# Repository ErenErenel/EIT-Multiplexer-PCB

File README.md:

# EIT Multiplexer PCB

EE499 Capstone Project — Low-power analog multiplexer board for Electrical Impedance Tomography (EIT).

## Overview

This board drives a 16-channel analog multiplexer (ADG1606) controlled by an RP2040 microcontroller. It is designed for EIT data acquisition, where the multiplexer selects electrode channels to inject current and measure voltage.

**Key ICs:**
- Raspberry Pi RP2040 — microcontroller
- ADG1606 — 16:1 analog multiplexer
- AP2112K — 5V to 3.3V LDO regulator
- LM27761 — negative voltage converter (for symmetric supply)

## Repository Structure

```
Hardware/         — KiCad project files (.kicad_pro, .kicad_sch, .kicad_pcb)
                    Custom footprint and symbol libraries bundled for portability
Production/
  Gerbers/        — Gerber files + drill files ready for PCB fabrication
  BOM/            — Bill of Materials (CSV and XLSX)
Docs/             — Schematic PDF, assembly drawing, component datasheets
```

## Opening the Design

1. Open **KiCad** (v7 or later)
2. Open `Hardware/EIT_Multiplexer.kicad_pro`
3. All custom libraries load automatically via relative paths — no manual configuration needed

## Fabrication

Gerber files are in `Production/Gerbers/`. The board is 2-layer FR4. Upload the contents of that folder (or `EIT_Multiplexer-job.gbrjob`) to your preferred PCB fab (JLCPCB, PCBWay, OSH Park, etc.).

## License

Hardware design files licensed under [CERN Open Hardware Licence v2 – Strongly Reciprocal (CERN-OHL-S)](LICENSE).

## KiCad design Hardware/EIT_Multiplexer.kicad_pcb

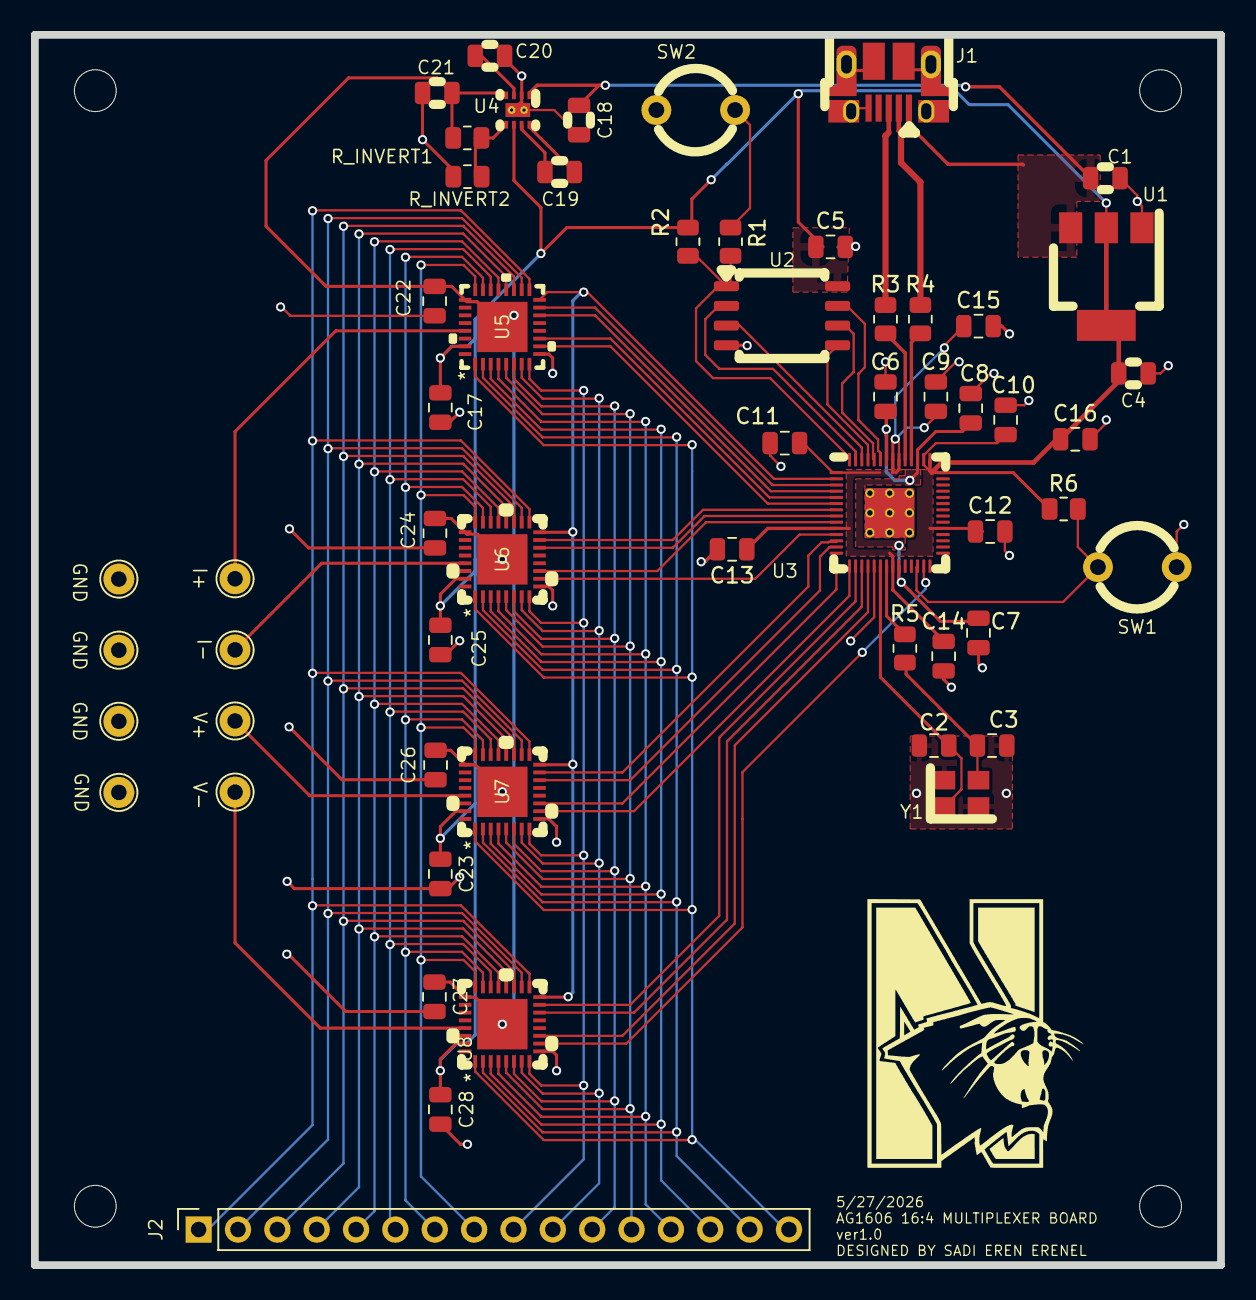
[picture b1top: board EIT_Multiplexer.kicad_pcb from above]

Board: 2 copper layers, 76.5 x 79.4 mm, 61 parts (0 on the bottom side), 61 nets.

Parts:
C1, C4: 10u; C_0805_2012Metric
C2, C3: 15p; C_0805_2012Metric
C5, C6, C7, C9, C11, C12, C13, C14, C15, C16, C17, C22, C23, C24, C25, C26, C27, C28: 100n; C_0805_2012Metric
C8, C10, C19: 1u; C_0805_2012Metric
C18, C20: 4.7u; C_0805_2012Metric
C21: 2.2u; C_0805_2012Metric
GND: Conn_01x01_Pin; TestPoint_THTPad_D2.0mm_Drill1.0mm
GND#2, GND#3, GND#4: Conn_01x01_Pin; TestPoint_THTPad_D2.0mm_Drill1.0mm
H1, H2, H3, H4: MountingHole; MountingHole_2.7mm_M2.5
I+: Conn_01x01_Pin; TestPoint_THTPad_D2.0mm_Drill1.0mm
I-: Conn_01x01_Pin; TestPoint_THTPad_D2.0mm_Drill1.0mm
J1: USB_B_Micro; USB_Micro-B_Amphenol_10103594-0001LF_Horizontal_modified
J2: Conn_01x16_Pin; PinSocket_1x16_P2.54mm_Vertical
R1, R5: 1k; R_0805_2012Metric
R2, R6: 10k; R_0805_2012Metric
R3, R4: 27; R_0805_2012Metric
R_INVERT1, R_INVERT2: R; R_0805_2012Metric
SW1, SW2: SW_Push; pushbutton (1)
U1: NCP1117-3.3_SOT223; SOT-223-3_TabPin2
U2: W25Q128JVS; SOIC-8_5.3x5.3mm_P1.27mm
U3: RP2040; RP2040-QFN-56
U4: LM27761DSGR; DSG0008A
U5, U6, U7, U8: ADG1606BCPZ-REEL7; CP_32_2_ADI
V+: Conn_01x01_Pin; TestPoint_THTPad_D2.0mm_Drill1.0mm
V-: Conn_01x01_Pin; TestPoint_THTPad_D2.0mm_Drill1.0mm
Y1: ABM8-272-T3; Crystal_SMD_3225-4Pin_3.2x2.5mm

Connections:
+1V1: C6.1, C7.1, C8.1, U3.23 (DVDD), U3.45 (VREG_VOUT), U3.50 (DVDD)
+3V3: C4.1, C5.1, C9.1, C10.1, C11.1, C12.1, C13.1, C14.1, C15.1, C16.1, C17.1, C23.1, C25.1, C28.1, R2.1, R6.1, U1.2 (VO), U2.8 (VCC), U3.1 (IOVDD), U3.10 (IOVDD), U3.22 (IOVDD), U3.33 (IOVDD), U3.42 (IOVDD), U3.43 (ADC_AVDD), U3.44 (VREG_IN), U3.48 (USB_VDD), U3.49 (IOVDD), U4.6 (EN), U5.31 (VDD), U6.31 (VDD), U7.31 (VDD), U8.31 (VDD)
-3V3: C21.1, C22.1, C24.1, C26.1, C27.1, R_INVERT1.1, U4.4 (VOUT), U5.25 (VSS), U5.33 (EPAD), U6.25 (VSS), U6.33 (EPAD), U7.25 (VSS), U7.33 (EPAD), U8.25 (VSS), U8.33 (EPAD)
/GPIO0: U3.2 (GPIO0), U5.16 (EN), U6.16 (EN), U7.16 (EN), U8.16 (EN)
/GPIO1: U3.3 (GPIO1), U5.15 (A0)
/GPIO2: U3.4 (GPIO2), U5.14 (A1)
/GPIO3: U3.5 (GPIO3), U5.11 (A2)
/GPIO4: U3.6 (GPIO4), U5.10 (A3)
/GPIO5: U3.7 (GPIO5), U6.15 (A0)
/GPIO6: U3.8 (GPIO6), U6.14 (A1)
/GPIO7: U3.9 (GPIO7), U6.11 (A2)
/GPIO8: U3.11 (GPIO8), U6.10 (A3)
/GPIO9: U3.12 (GPIO9), U7.15 (A0)
/GPIO10: U3.13 (GPIO10), U7.14 (A1)
/GPIO11: U3.14 (GPIO11), U7.11 (A2)
/GPIO12: U3.15 (GPIO12), U7.10 (A3)
/GPIO13: U3.16 (GPIO13), U8.15 (A0)
/GPIO14: U3.17 (GPIO14), U8.14 (A1)
/GPIO15: U3.18 (GPIO15), U8.11 (A2)
/GPIO16: U3.27 (GPIO16), U8.10 (A3)
/I+: I+.1, U5.29 (D)
/I-: I-.1, U6.29 (D)
/QSPI_SCLK: U2.6 (CLK), U3.52 (QSPI_SCLK)
/QSPI_SD0: U2.5 (DI(IO0)), U3.53 (QSPI_SD0)
/QSPI_SD1: U2.2 (DO(IO1)), U3.55 (QSPI_SD1)
/QSPI_SD2: U2.3 (IO2), U3.54 (QSPI_SD2)
/QSPI_SD3: U2.7 (IO3), U3.51 (QSPI_SD3)
/QSPI_SS: R1.1, R2.2, U2.1 (~CS), U3.56 (QSPI_SS)
/S1: J2.1, U5.17 (S1), U6.17 (S1), U7.17 (S1), U8.17 (S1)
/S2: J2.2, U5.18 (S2), U6.18 (S2), U7.18 (S2), U8.18 (S2)
/S3: J2.3, U5.19 (S3), U6.19 (S3), U7.19 (S3), U8.19 (S3)
/S4: J2.4, U5.20 (S4), U6.20 (S4), U7.20 (S4), U8.20 (S4)
/S5: J2.5, U5.21 (S5), U6.21 (S5), U7.21 (S5), U8.21 (S5)
/S6: J2.6, U5.22 (S6), U6.22 (S6), U7.22 (S6), U8.22 (S6)
/S7: J2.7, U5.23 (S7), U6.23 (S7), U7.23 (S7), U8.23 (S7)
/S8: J2.8, U5.24 (S8), U6.24 (S8), U7.24 (S8), U8.24 (S8)
/S9: J2.9, U5.8 (S9), U6.8 (S9), U7.8 (S9), U8.8 (S9)
/S10: J2.10, U5.7 (S10), U6.7 (S10), U7.7 (S10), U8.7 (S10)
/S11: J2.11, U5.6 (S11), U6.6 (S11), U7.6 (S11), U8.6 (S11)
/S12: J2.12, U5.5 (S12), U6.5 (S12), U7.5 (S12), U8.5 (S12)
/S13: J2.13, U5.4 (S13), U6.4 (S13), U7.4 (S13), U8.4 (S13)
/S14: J2.14, U5.3 (S14), U6.3 (S14), U7.3 (S14), U8.3 (S14)
/S15: J2.15, U5.2 (S15), U6.2 (S15), U7.2 (S15), U8.2 (S15)
/S16: J2.16, U5.1 (S16), U6.1 (S16), U7.1 (S16), U8.1 (S16)
/USB_D+: J1.3 (D+), R3.1
/USB_D-: J1.2 (D-), R4.1
/V+: U7.29 (D), V+.1
/V-: U8.29 (D), V-.1
/XIN: C2.1, U3.20 (XIN), Y1.1
/XOUT: R5.1, U3.21 (XOUT)
/~USB_BOOT: R1.2, SW2.2
GND: C1.2, C2.2, C3.2, C4.2, C5.2, C6.2, C7.2, C8.2, C9.2, C10.2, C11.2, C12.2, C13.2, C14.2, C15.2, C16.2, C17.2, C18.2, C20.2, C21.2, C22.2, C23.2, C24.2, C25.2, C26.2, C27.2, C28.2, GND.1, GND#2.1, GND#3.1, GND#4.1, J1.5 (GND), J1.6 (Shield), R_INVERT2.2, SW1.2, SW2.1, U1.1 (GND), U2.4 (GND), U3.19 (TESTEN), U3.57 (GND), U4.2 (GND), U4.9 (PAD), U4.V, U5.9 (GND), U6.9 (GND), U7.9 (GND), U8.9 (GND), Y1.2, Y1.4
unnamed: C3.1, R5.2, Y1.3
unnamed: R6.2, SW1.1, U3.26 (RUN)
unnamed: R4.2, U3.46 (USB_DM)
unnamed: R3.2, U3.47 (USB_DP)
unnamed: C19.2, U4.8 (C1+)
unnamed: C19.1, U4.7 (C1-)
unnamed: C20.1, U4.3 (CPOUT)
unnamed: R_INVERT1.2, R_INVERT2.1, U4.5 (VFB)
VBUS: C1.1, C18.1, J1.1 (VBUS), U1.3 (VI), U4.1 (VIN)

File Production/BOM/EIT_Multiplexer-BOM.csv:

"Id";"Designator";"Footprint";"Quantity";"Designation";"Supplier and ref";
1;"R_INVERT2,R_INVERT1";"R_0805_2012Metric";2;"R";;;
2;"GND,I+,GND,I-,GND,V+,GND,V-";"TestPoint_THTPad_D2.0mm_Drill1.0mm";8;"Conn_01x01_Pin";;;
3;"C4,C1";"C_0805_2012Metric";2;"10u";;;
4;"J1";"USB_Micro-B_Amphenol_10103594-0001LF_Horizontal_modified";1;"USB_B_Micro";;;
5;"C10,C8";"C_0402_1005Metric";2;"1u";;;
6;"C13,C5,C9,C12,C14,C7,C11,C16,C6,C15";"C_0402_1005Metric";10;"100n";;;
7;"R2,R6";"R_0402_1005Metric";2;"10k";;;
8;"U1";"SOT-223-3_TabPin2";1;"NCP1117-3.3_SOT223";;;
9;"U2";"SOIC-8_5.3x5.3mm_P1.27mm";1;"W25Q128JVS";;;
10;"R1,R5";"R_0402_1005Metric";2;"1k";;;
11;"R3,R4";"R_0402_1005Metric";2;"27";;;
12;"U3";"RP2040-QFN-56";1;"RP2040";;;
13;"U4";"DSG0008A";1;"LM27761DSGR";;;
14;"C18,C20";"C_0805_2012Metric";2;"4.7u";;;
15;"C23,C26,C22,C25,C24,C28,C17,C27";"C_0805_2012Metric";8;"100n";;;
16;"H3,H2,H4,H1";"MountingHole_2.7mm_M2.5";4;"MountingHole";;;
17;"C2,C3";"C_0402_1005Metric";2;"15p";;;
18;"C21";"C_0805_2012Metric";1;"2.2u";;;
19;"C19";"C_0805_2012Metric";1;"1u";;;
20;"SW2,SW1";"pushbutton (1)";2;"SW_Push";;;
21;"Y1";"Crystal_SMD_3225-4Pin_3.2x2.5mm";1;"ABM8-272-T3";;;
22;"U8,U7,U5,U6";"CP_32_2_ADI";4;"ADG1606BCPZ-REEL7";;;
23;"J2";"PinSocket_1x16_P2.54mm_Vertical";1;"Conn_01x16_Pin";;;

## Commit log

2026-06-12 Initial commit: EIT Multiplexer PCB design files
    KiCad project for EE499 capstone — 16-channel ADG1606 multiplexer board
    with RP2040 microcontroller for Electrical Impedance Tomography.
    Includes: KiCad source files, bundled custom libraries, Gerbers, BOM, and docs.
2026-06-12 Update Excel BOM to match KiCad CSV export
    Added missing components: 4x ADG1606, LM27761, 100nF 0805 bypass caps,
    4.7uF caps, test points, mounting holes, push buttons, corrected connector.
    Removed stale J3/J4 headers from old revision. Kept manufacturer part
    numbers from original Excel where designators matched.
2026-06-25 Replace schematic and PCB layout PDFs with correct final versions
2026-06-25 Remove datasheets and assembly PDF from Docs
